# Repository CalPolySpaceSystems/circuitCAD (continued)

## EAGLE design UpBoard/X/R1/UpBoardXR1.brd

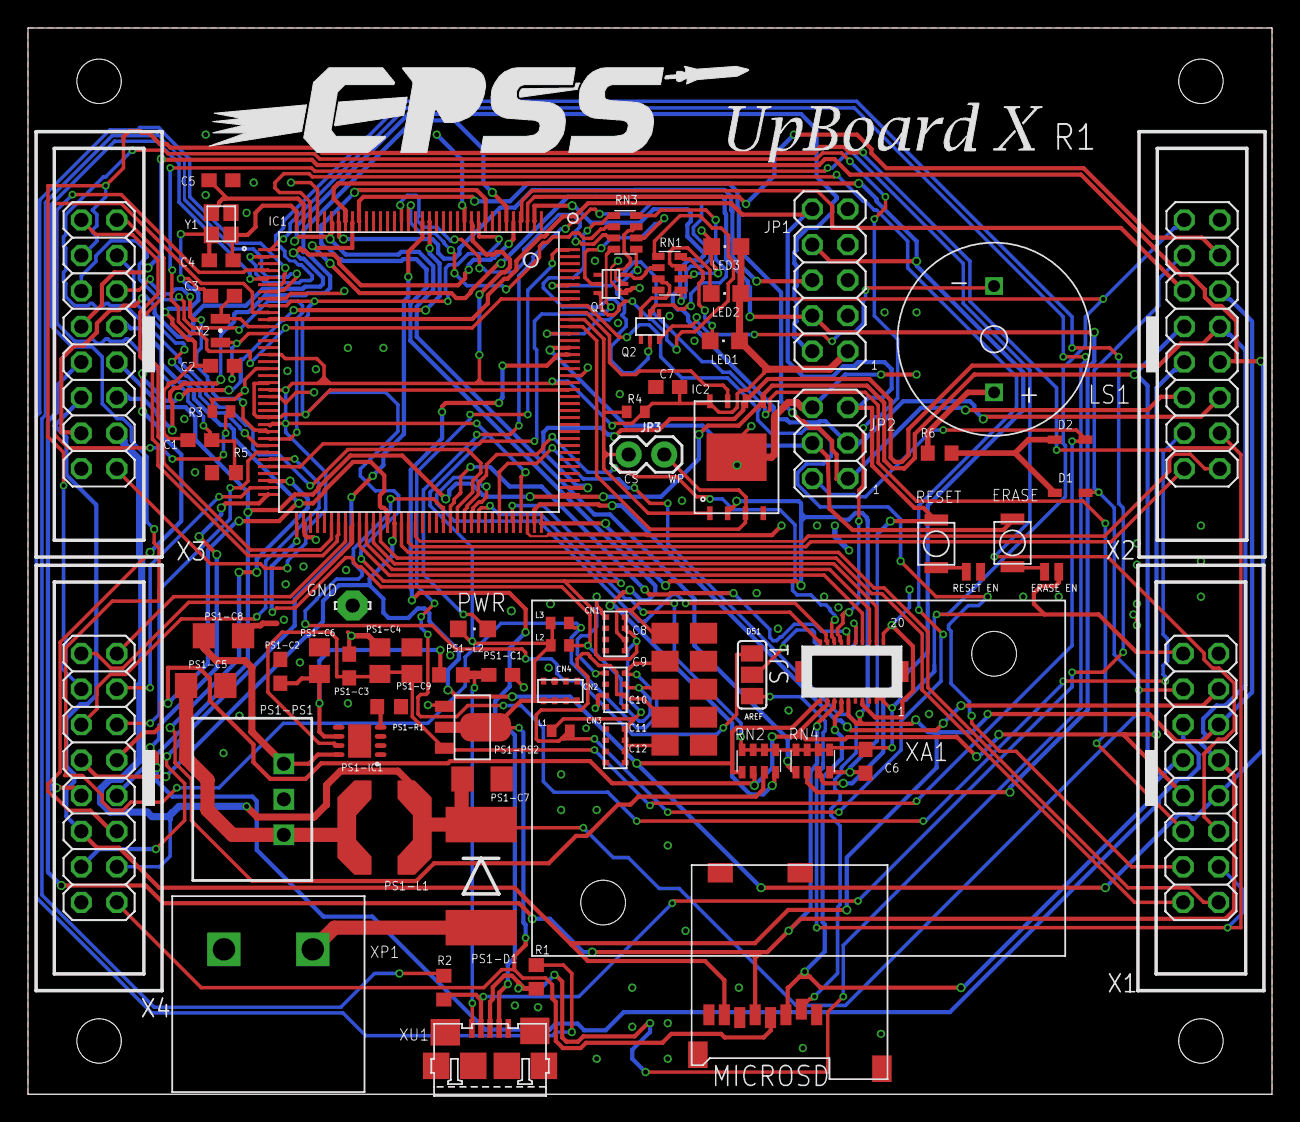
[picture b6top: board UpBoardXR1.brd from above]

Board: 2 copper layers, 88.9 x 76.2 mm, 75 parts (0 on the bottom side), 101 nets.

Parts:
C1: 10pF; C0603
C2, C3, C4, C5: 22pF; C0603
C6: 10n; C0603
C7: 100n; C0603
C8, C9, C10, C11, C12: 10uF; A/3216-18R
CN1, CN2, CN3, CN4: 100nF; 1206-4
D1, D2: SOD323
ERASE: 1000P; B3U-1000P
GND: LSP10
IC1: SAM3X8E(ARDUINO); 144-LEAD_LQFP
IC2: W25N01GVZEIG/IT; WSON
JP1: JTAG; 2X05
JP2: CONFIG; 2X03
JP3: 1X02
L1, L2, L3: C0402
LED1, LED2, LED3: CHIPLED_0805
LS1: AI-1440-TWT-24V-2-R; AI-1440-TWT-24-2-R
PS1-1:C1: 10nF; C0603
PS1-1:C2, PS1-1:C3: 100nF; C0603
PS1-1:C4: 1uF; C0805
PS1-1:C5: 4.7uF; C1206
PS1-1:C6: 4.7uF; C0805
PS1-1:C7, PS1-1:C8: 10uF; C1206
PS1-1:C9: 100uF; C0805
PS1-1:D1: S10M-TP; DO-214AB
PS1-1:IC1: TPS2115ADRB; SON-8
PS1-1:L1: LPS6225-103MRB; INDM600X600X240N
PS1-1:L2: Wurth 742792641; R0603
PS1-1:PS1: R-78E5.0-1.0
PS1-1:PS2: AZ1117C; SOT89
PS1-1:R1: 330; R0603
PWR: CHIPLED_0805
Q1, Q2: MBT3904DW2T1; SOT-363
R1, R2: 39; R0603
R3, R4: 220R; R0402
R5: 6.8K; R0603
R6: 0R; R0603
RESET: 1000P; B3U-1000P
RN1: 65R; CTS742C083
RN2, RN3: 4.7K; CTS742C083
RN4: 100K; CTS742C083
SD1: CONN_MICROSD
SJ1: SJ_2
SJ2, SJ3: SOLBRDG
X1, X2, X3, X4: 16POS_RIBBON; 2X08
XA1: DF12-20PIN_CONNECTOR_HEADER; DF12-HEADER
XP1: 2POSTERMINALBLOCK.25"PITCH; OSTYK22102030
XU1: MICROUSB_5POS_SMT; RECPT_SMT_R/A
Y1: FH1200001; MINISMD
Y2: ABS05; FC-12M

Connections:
1.8V: C12.+, CN1.P$1, CN1.P$2, CN3.P$1, CN3.P$2, CN3.P$3, CN3.P$4, IC1.P$10, IC1.P$45, IC1.P$56, IC1.P$61, IC1.P$104, IC1.P$124, L1.1
3.3V: C6.1, C7.2, C8.+, CN1.P$3, CN1.P$4, CN4.P$1, CN4.P$2, CN4.P$3, CN4.P$4, IC1.P$11, IC1.P$52, IC1.P$57, IC1.P$62, IC1.P$105, IC1.P$125, IC2.P8, JP1.1, L2.1, L3.1, LED1.A, LED2.A, LED3.A, PS1-1:PS2.2, PS1-1:PS2.2@1, PWR.A, R4.2, RN2.5, RN2.6, RN2.7, RN2.8, RN4.5, RN4.6, RN4.7, RN4.8, SD1.4, SJ3.P$2, X1.1, X2.1, X3.1, X4.1, XA1.P$1, XA1.P$2
5V: D2.2, JP2.2, PS1-1:C3.1, PS1-1:C4.1, PS1-1:C9.1, PS1-1:IC1.7, PS1-1:PS2.3
A0: IC1.P$78, X3.15
A1: IC1.P$79, X3.16
A2: IC1.P$80, X4.15
A3: IC1.P$81, X4.16
A4: IC1.P$82, XA1.P$17
A5: IC1.P$83, XA1.P$18
A6: IC1.P$84, XA1.P$19
A7: IC1.P$85, X1.15
A8: IC1.P$88, X1.16
A9: IC1.P$89, X2.15
A10: IC1.P$90, X2.16
AREF: SJ1.3, X1.14, X2.14, X3.14, X4.14
AREF0/D51: SJ1.2, XA1.P$16
D2: IC1.P$144, X2.13
D3: IC1.P$139, X1.11
D4: IC1.P$137, X1.12
D5: IC1.P$136, X1.13
D6: IC1.P$135, IC2.P7
D7: IC1.P$134, IC2.P1, JP3.1, R4.1
D8: IC1.P$133, IC2.P3, JP3.2
D9: IC1.P$132, RN3.1
D10: IC1.P$102, SD1.2
D11: IC1.P$20, RN3.2
D12: IC1.P$21, RN3.3
D13: IC1.P$68, RN3.4
D37: IC1.P$63, X3.11
D38: IC1.P$64, X3.12
D39: IC1.P$65, X3.13
D40: IC1.P$66, X4.11
D41: IC1.P$67, X4.12
D42: IC1.P$71, X4.13
D46: IC1.P$99, XA1.P$11
D47: IC1.P$98, XA1.P$12
D48: IC1.P$97, XA1.P$13
D49: IC1.P$96, XA1.P$14
D50: IC1.P$95, XA1.P$15
D51: IC1.P$94, SJ1.1
D+: IC1.P$37, R1.1, XU1.P3
D-: IC1.P$38, R2.1, XU1.P2
ERASE: ERASE.P$2, IC1.P$130, JP2.4
GND: C1.2, C2.2, C3.2, C4.1, C5.1, C7.1, C8.-, C9.-, C10.-, C11.-, C12.-, CN1.P$5, CN1.P$6, CN1.P$7, CN1.P$8, CN2.P$2, CN2.P$3, CN2.P$4, CN3.P$5, CN3.P$6, CN3.P$7, CN3.P$8, CN4.P$5, CN4.P$6, CN4.P$7, CN4.P$8, GND.MP, IC1.P$12, IC1.P$33, IC1.P$44, IC1.P$54, IC1.P$58, IC1.P$74, IC1.P$106, IC1.P$126, IC2.P4, IC2.TH, JP1.3, JP1.5, JP1.9, JP2.6, PS1-1:C1.2, PS1-1:C2.2, PS1-1:C3.2, PS1-1:C4.2, PS1-1:C5.2, PS1-1:C6.2, PS1-1:C7.2, PS1-1:C8.2, PS1-1:C9.2, PS1-1:IC1.3, PS1-1:IC1.5, PS1-1:IC1.PAD, PS1-1:PS1.2, PS1-1:PS2.1, PS1-1:R1.2, Q1.P$1, Q1.P$4, Q2.P$1, Q2.P$4, R3.2, R5.1, RN1.8, SD1.6, SD1.GND1, SD1.GND2, SD1.GND3, SJ2.P$2, X1.2, X2.2, X3.2, X4.2, XA1.P$4, XA1.P$5, XA1.P$20, XP1.P$2, XU1.P5, Y1.GND2, Y1.GND4
HV: D1.2, PS1-1:C7.1, PS1-1:D1.-, PS1-1:L1.1, X1.3, X2.3, X3.3, X4.3
JTAG_SEL: IC1.P$46, R3.1
JTAG_TCK: IC1.P$28, JP1.4, RN4.2
JTAG_TDI: IC1.P$29, JP1.8, RN4.3
JTAG_TDO: IC1.P$30, JP1.6
JTAG_TMS: IC1.P$31, JP1.2, RN4.1
LS_DRIVE: D1.1, D2.1, R6.2
MISO: IC1.P$108, IC2.P2, SD1.7, X1.6, X2.6, X3.6, X4.6, XA1.P$6
MOSI: IC1.P$109, IC2.P5, SD1.3, X1.7, X2.7, X3.7, X4.7, XA1.P$7
M_RESET: C6.2, IC1.P$47, JP1.10, JP2.5, RESET.P$2, RN4.4
unnamed: LED3.C, RN1.2
unnamed: IC1.P$42, R1.2
unnamed: LED2.C, RN1.3
unnamed: PS1-1:D1.+, XP1.P$1
unnamed: PWR.C, RN1.1
unnamed: RESET.P$1, SJ2.P$1
unnamed: LED1.C, RN1.4
unnamed: Q2.P$5, RN3.5
unnamed: IC1.P$43, R2.2
unnamed: Q2.P$3, RN1.7
unnamed: Q1.P$6, RN1.6
unnamed: Q1.P$3, RN1.5
unnamed: Q1.P$2, RN3.6
unnamed: Q1.P$5, RN3.7
unnamed: Q2.P$2, RN3.8
unnamed: ERASE.P$1, SJ3.P$1
unnamed: C5.2, IC1.P$35, Y1.P3
unnamed: LS1.-, Q2.P$6
unnamed: C4.2, IC1.P$36, Y1.P1
unnamed: C2.1, IC1.P$49, Y2.2
unnamed: C3.1, IC1.P$48, Y2.1
unnamed: LS1.+, R6.1
unnamed: C1.1, IC1.P$40, R5.2
PS1-1:BATT_5V: PS1-1:C8.1, PS1-1:IC1.8, PS1-1:PS1.3
PS1-1:N$2: PS1-1:C5.1, PS1-1:L1.2, PS1-1:PS1.1
PS1-1:N$3: PS1-1:IC1.4, PS1-1:R1.1
PS1-1:USB_FILTERED: PS1-1:C2.1, PS1-1:C6.1, PS1-1:IC1.6, PS1-1:L2.2
RX/D0: IC1.P$27, JP2.1, X2.11
RXS0: IC1.P$3, X2.4
RXS1: IC1.P$5, X3.4
RXS2: IC1.P$107, X1.4
RXS3: IC1.P$18, X4.4
SCK: IC1.P$110, IC2.P6, SD1.5, X1.8, X2.8, X3.8, X4.8, XA1.P$8
SCL: IC1.P$87, RN2.1, X1.10, X2.10, X3.10, X4.10, XA1.P$10
SCL1: IC1.P$70, RN2.3
SDA: IC1.P$86, RN2.2, X1.9, X2.9, X3.9, X4.9, XA1.P$9
SDA1: IC1.P$9, RN2.4
TX/D1: IC1.P$2, JP2.3, X2.12
TXS0: IC1.P$4, X2.5
TXS1: IC1.P$6, X3.5
TXS2: IC1.P$72, X1.5
TXS3: IC1.P$17, X4.5
UOTGID: IC1.P$129, XU1.P4
VBUS: PS1-1:C1.1, PS1-1:L2.1, XU1.P1
VDDANA: C10.+, CN2.P$7, IC1.P$73, L2.2
VDDPLL: C11.+, CN2.P$6, IC1.P$34, L1.2
VDDUTMI: C9.+, CN2.P$8, IC1.P$41, L3.2
